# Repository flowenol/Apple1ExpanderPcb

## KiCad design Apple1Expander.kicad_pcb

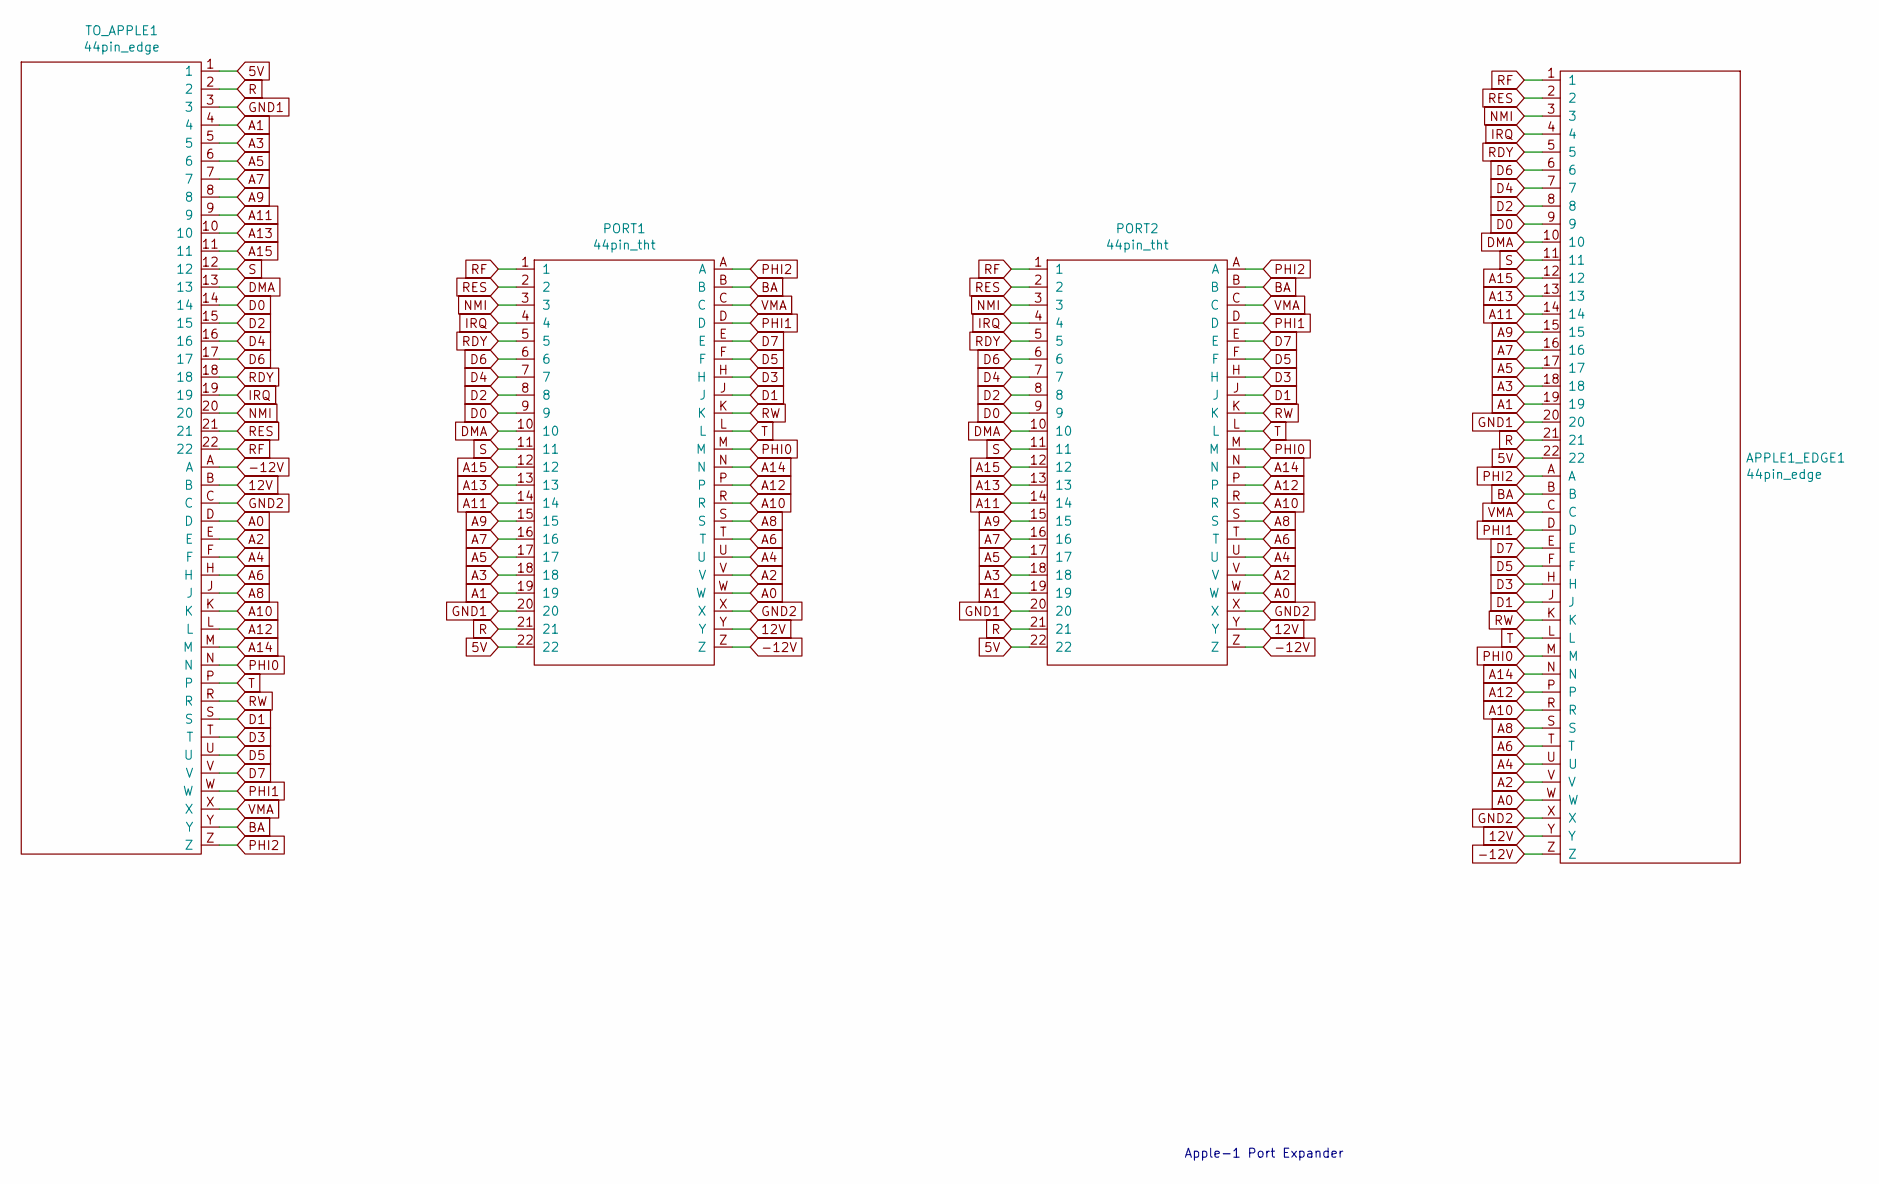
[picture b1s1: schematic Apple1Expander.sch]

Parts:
APPLE1_EDGE1: 44pin_edge; 44pin1
PORT1, PORT2: 44pin_tht; 44pin_socket
TO_APPLE1: 44pin_edge; 44pin1

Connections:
5V: APPLE1_EDGE1.22, PORT1.22, PORT2.22, TO_APPLE1.1
12V: APPLE1_EDGE1.Y, PORT1.Y, PORT2.Y, TO_APPLE1.B
-12V: APPLE1_EDGE1.Z, PORT1.Z, PORT2.Z, TO_APPLE1.A
A0: APPLE1_EDGE1.W, PORT1.W, PORT2.W, TO_APPLE1.D
A1: APPLE1_EDGE1.19, PORT1.19, PORT2.19, TO_APPLE1.4
A2: APPLE1_EDGE1.V, PORT1.V, PORT2.V, TO_APPLE1.E
A3: APPLE1_EDGE1.18, PORT1.18, PORT2.18, TO_APPLE1.5
A4: APPLE1_EDGE1.U, PORT1.U, PORT2.U, TO_APPLE1.F
A5: APPLE1_EDGE1.17, PORT1.17, PORT2.17, TO_APPLE1.6
A6: APPLE1_EDGE1.T, PORT1.T, PORT2.T, TO_APPLE1.H
A7: APPLE1_EDGE1.16, PORT1.16, PORT2.16, TO_APPLE1.7
A8: APPLE1_EDGE1.S, PORT1.S, PORT2.S, TO_APPLE1.J
A9: APPLE1_EDGE1.15, PORT1.15, PORT2.15, TO_APPLE1.8
A10: APPLE1_EDGE1.R, PORT1.R, PORT2.R, TO_APPLE1.K
A11: APPLE1_EDGE1.14, PORT1.14, PORT2.14, TO_APPLE1.9
A12: APPLE1_EDGE1.P, PORT1.P, PORT2.P, TO_APPLE1.L
A13: APPLE1_EDGE1.13, PORT1.13, PORT2.13, TO_APPLE1.10
A14: APPLE1_EDGE1.N, PORT1.N, PORT2.N, TO_APPLE1.M
A15: APPLE1_EDGE1.12, PORT1.12, PORT2.12, TO_APPLE1.11
BA: APPLE1_EDGE1.B, PORT1.B, PORT2.B, TO_APPLE1.Y
D0: APPLE1_EDGE1.9, PORT1.9, PORT2.9, TO_APPLE1.14
D1: APPLE1_EDGE1.J, PORT1.J, PORT2.J, TO_APPLE1.S
D2: APPLE1_EDGE1.8, PORT1.8, PORT2.8, TO_APPLE1.15
D3: APPLE1_EDGE1.H, PORT1.H, PORT2.H, TO_APPLE1.T
D4: APPLE1_EDGE1.7, PORT1.7, PORT2.7, TO_APPLE1.16
D5: APPLE1_EDGE1.F, PORT1.F, PORT2.F, TO_APPLE1.U
D6: APPLE1_EDGE1.6, PORT1.6, PORT2.6, TO_APPLE1.17
D7: APPLE1_EDGE1.E, PORT1.E, PORT2.E, TO_APPLE1.V
DMA: APPLE1_EDGE1.10, PORT1.10, PORT2.10, TO_APPLE1.13
GND1: APPLE1_EDGE1.20, PORT1.20, PORT2.20, TO_APPLE1.3
GND2: APPLE1_EDGE1.X, PORT1.X, PORT2.X, TO_APPLE1.C
IRQ: APPLE1_EDGE1.4, PORT1.4, PORT2.4, TO_APPLE1.19
NMI: APPLE1_EDGE1.3, PORT1.3, PORT2.3, TO_APPLE1.20
PHI0: APPLE1_EDGE1.M, PORT1.M, PORT2.M, TO_APPLE1.N
PHI1: APPLE1_EDGE1.D, PORT1.D, PORT2.D, TO_APPLE1.W
PHI2: APPLE1_EDGE1.A, PORT1.A, PORT2.A, TO_APPLE1.Z
R: APPLE1_EDGE1.21, PORT1.21, PORT2.21, TO_APPLE1.2
RDY: APPLE1_EDGE1.5, PORT1.5, PORT2.5, TO_APPLE1.18
RES: APPLE1_EDGE1.2, PORT1.2, PORT2.2, TO_APPLE1.21
RF: APPLE1_EDGE1.1, PORT1.1, PORT2.1, TO_APPLE1.22
RW: APPLE1_EDGE1.K, PORT1.K, PORT2.K, TO_APPLE1.R
S: APPLE1_EDGE1.11, PORT1.11, PORT2.11, TO_APPLE1.12
T: APPLE1_EDGE1.L, PORT1.L, PORT2.L, TO_APPLE1.P
VMA: APPLE1_EDGE1.C, PORT1.C, PORT2.C, TO_APPLE1.X

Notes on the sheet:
Apple-1 Port Expander

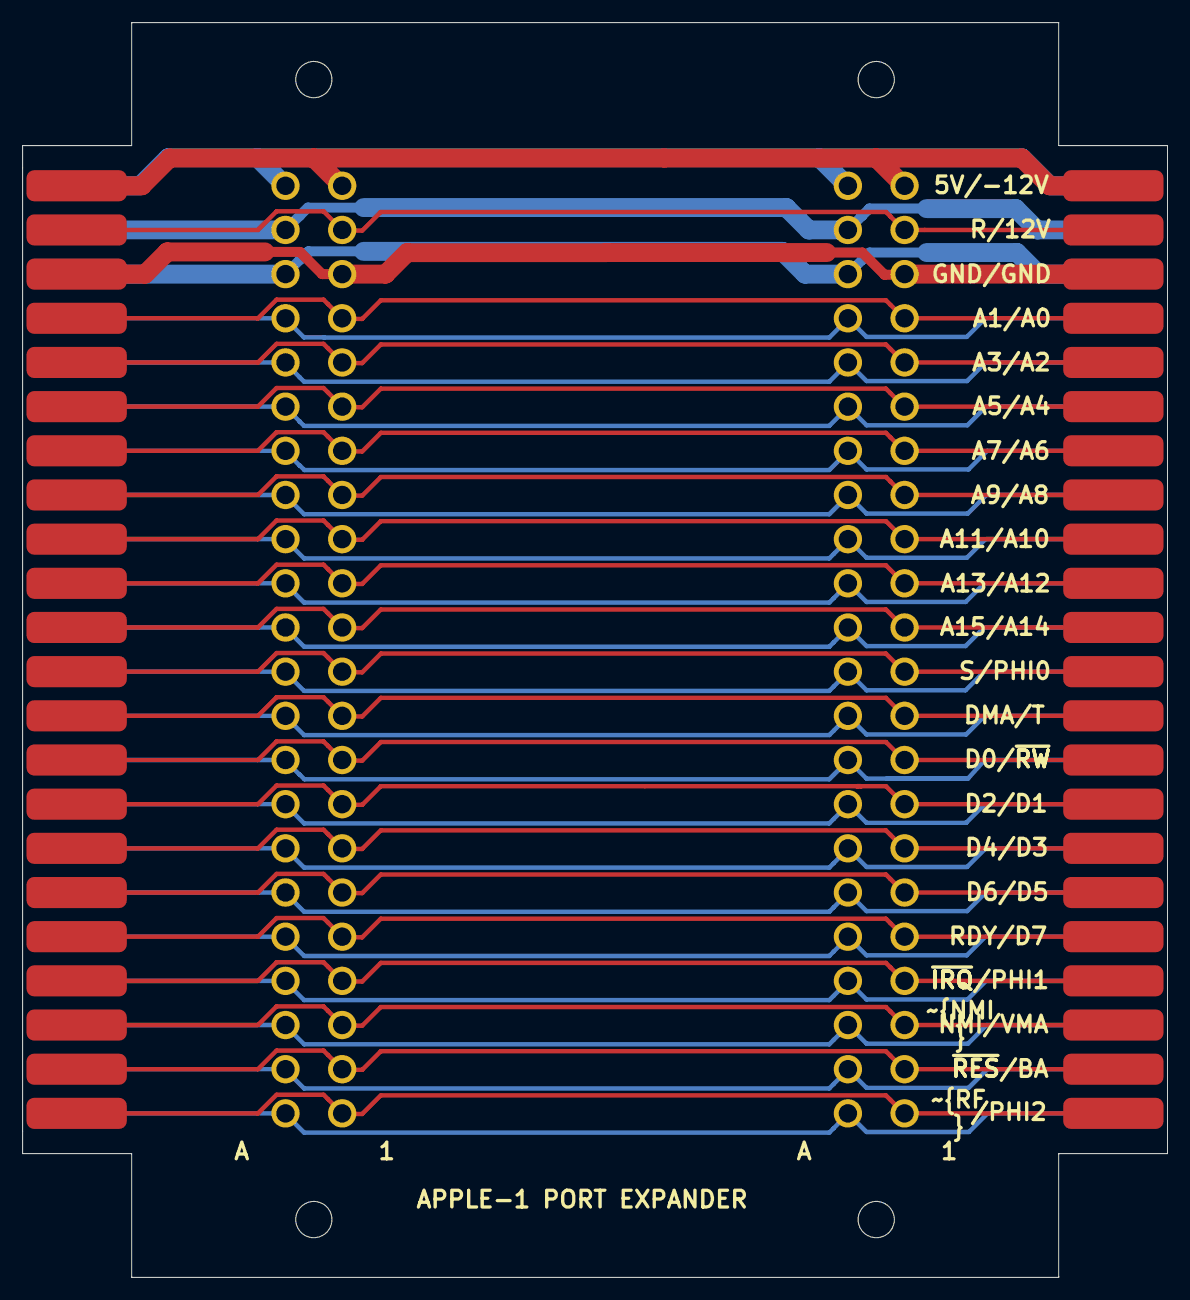
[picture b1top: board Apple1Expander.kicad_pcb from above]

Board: 2 copper layers, 102.6 x 112.5 mm, 4 parts (0 on the bottom side), 44 nets.

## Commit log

2020-07-12 small updates
2020-12-14 small fixes
2021-03-03 Added .gitignore
2021-03-18 Fixed libs path
